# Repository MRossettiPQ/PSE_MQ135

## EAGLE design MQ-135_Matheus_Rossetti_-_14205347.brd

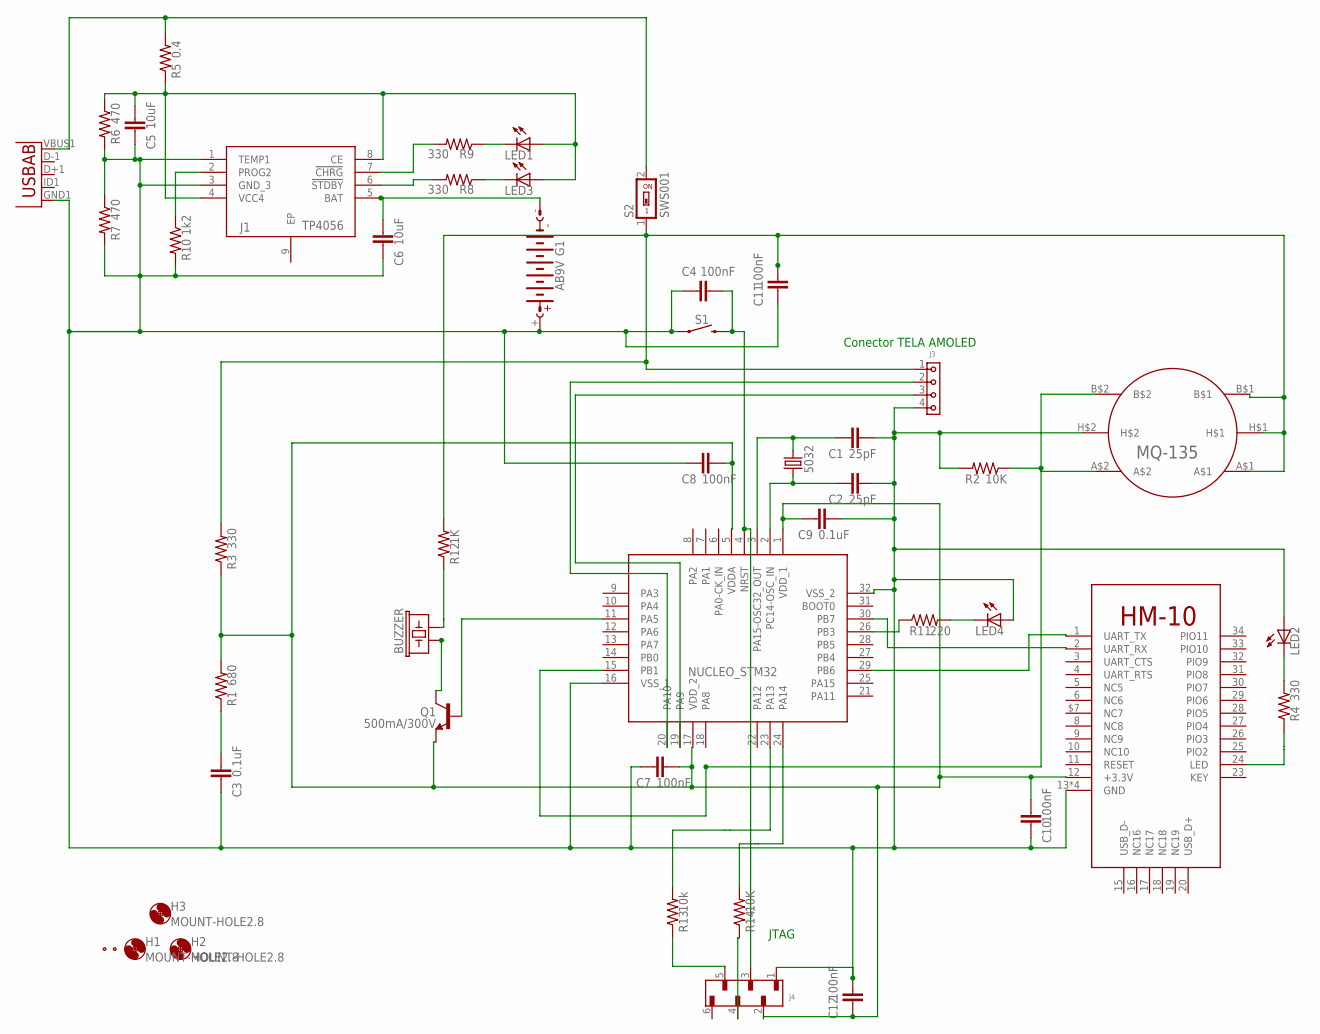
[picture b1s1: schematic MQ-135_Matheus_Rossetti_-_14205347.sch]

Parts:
BT_SENSOR: HM-10-BOARD; 26.9X13X2.2_BOARD
C1, C2: 25pF; CAP_0805
C3, C9: 0.1uF; CAP_0805
C4, C7, C8, C10, C11, C12: 100nF; CAP_0805
C5, C6: 10uF; CAP_0805
G1: AB9V
H1, H2, H3: MOUNT-HOLE2.8; 2,8
J1: TP4056; SOIC127P600X175-9N
J3: 6130XX11821_61300411821; 61300411821
J4: 6100XX18221_61000618221; 61000618221
LED1, LED2, LED3, LED4: LEDCHIP-LED0805; CHIP-LED0805
LS4: BUZZER; BUZZER-CCV-KIT
NUCLEO_STM32: STM32; QFP80P900X900X160-32N
Q1: 500mA/300V; SOT23-3
R1: 680; RES_0805
R2, R14: 10K; RES_0805
R3, R4, R8, R9: 330; RES_0805
R5: 0.4; RES_0805
R6, R7: 470; RES_0805
R10: 1k2; RES_0805
R11: 220; RES_0805
R12: 1K; RES_0805
R13: 10k; RES_0805
S1: MOMENTARY-SWITCH-SPST-SMD-6.0X3.5MM; TACTILE_SWITCH_SMD_6.0X3.5MM
S2: SWS001; SMS-001
U1: USB""; USB-MICRO-SMD
U$1: MQ_135_A; MQ-135
X1, X3: FIDUCIAL_0.6-1.2MM; FIDUCIAL0.6-1.2
X2: 5032; 5032/2P

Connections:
3,3V: BT_SENSOR.12 (+3.3V), C7.1, C8.1, C9.2, C10.1, C12.1, J4.2, NUCLEO_STM32.1 (VDD_1), NUCLEO_STM32.5 (VDDA), NUCLEO_STM32.17 (VDD_2), Q1.2 (E), R1.2, R3.1
5V: R5.2, S2.2, U1.VBUS1 (VBUS)
5V-SWT: C11.2, J3.1, R3.2, R12.2, S2.1, U$1.A$1, U$1.B$1, U$1.H$1
ENTRADASENSOR: NUCLEO_STM32.15 (PB1), R2.1, U$1.A$2, U$1.B$2
GND: BT_SENSOR.13 (GND), BT_SENSOR.14 (GND), BT_SENSOR.21 (GND), BT_SENSOR.22 (GND), C1.2, C2.2, C3.2, C4.1, C5.2, C6.1, C7.2, C8.2, C9.1, C10.2, C11.1, C12.2, G1.+, J1.1 (TEMP1), J1.3 (GND_3), J3.4, J4.1, LED2.A, LED4.A, NUCLEO_STM32.16 (VSS_1), NUCLEO_STM32.32 (VSS_2), R2.2, R6.2, R7.1, R7.2, R10.2, S1.1, U1.GND1 (GND), U$1.H$2
unnamed: NUCLEO_STM32.23 (PA13), R13.2
unnamed: NUCLEO_STM32.11 (PA5), Q1.1 (B)
unnamed: NUCLEO_STM32.24 (PA14), R14.2
unnamed: J4.5, R13.1
unnamed: NUCLEO_STM32.26 (PB3), R11.1
unnamed: BT_SENSOR.2 (UART_RX), NUCLEO_STM32.30 (PB7)
unnamed: BT_SENSOR.24 (LED), R4.1
unnamed: C1.1, NUCLEO_STM32.3 (PA15-OSC32_OUT), X2.2
unnamed: C6.2, G1.-, J1.5 (BAT)
unnamed: C2.1, NUCLEO_STM32.2 (PC14-OSC_IN), X2.1
unnamed: LED2.C, R4.2
unnamed: J3.2, NUCLEO_STM32.20 (PA10)
unnamed: C5.1, J1.4 (VCC4), J1.8 (CE), LED1.A, LED3.A, R5.1, R6.1
unnamed: J4.4, R14.1
unnamed: J3.3, NUCLEO_STM32.19 (PA9)
unnamed: J1.2 (PROG2), R10.1
unnamed: LED4.C, R11.2
unnamed: LS4.+ (1), Q1.3 (C)
unnamed: C3.1, R1.1
unnamed: LS4.- (2), R12.1
unnamed: BT_SENSOR.1 (UART_TX), NUCLEO_STM32.29 (PB6)
unnamed: J1.6 (!STDBY), R8.2
unnamed: J1.7 (!CHRG), R9.2
unnamed: LED1.C, R9.1
unnamed: LED3.C, R8.1
RST: C4.2, J4.3, NUCLEO_STM32.4 (NRST), S1.2

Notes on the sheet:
Conector TELA AMOLED
JTAG

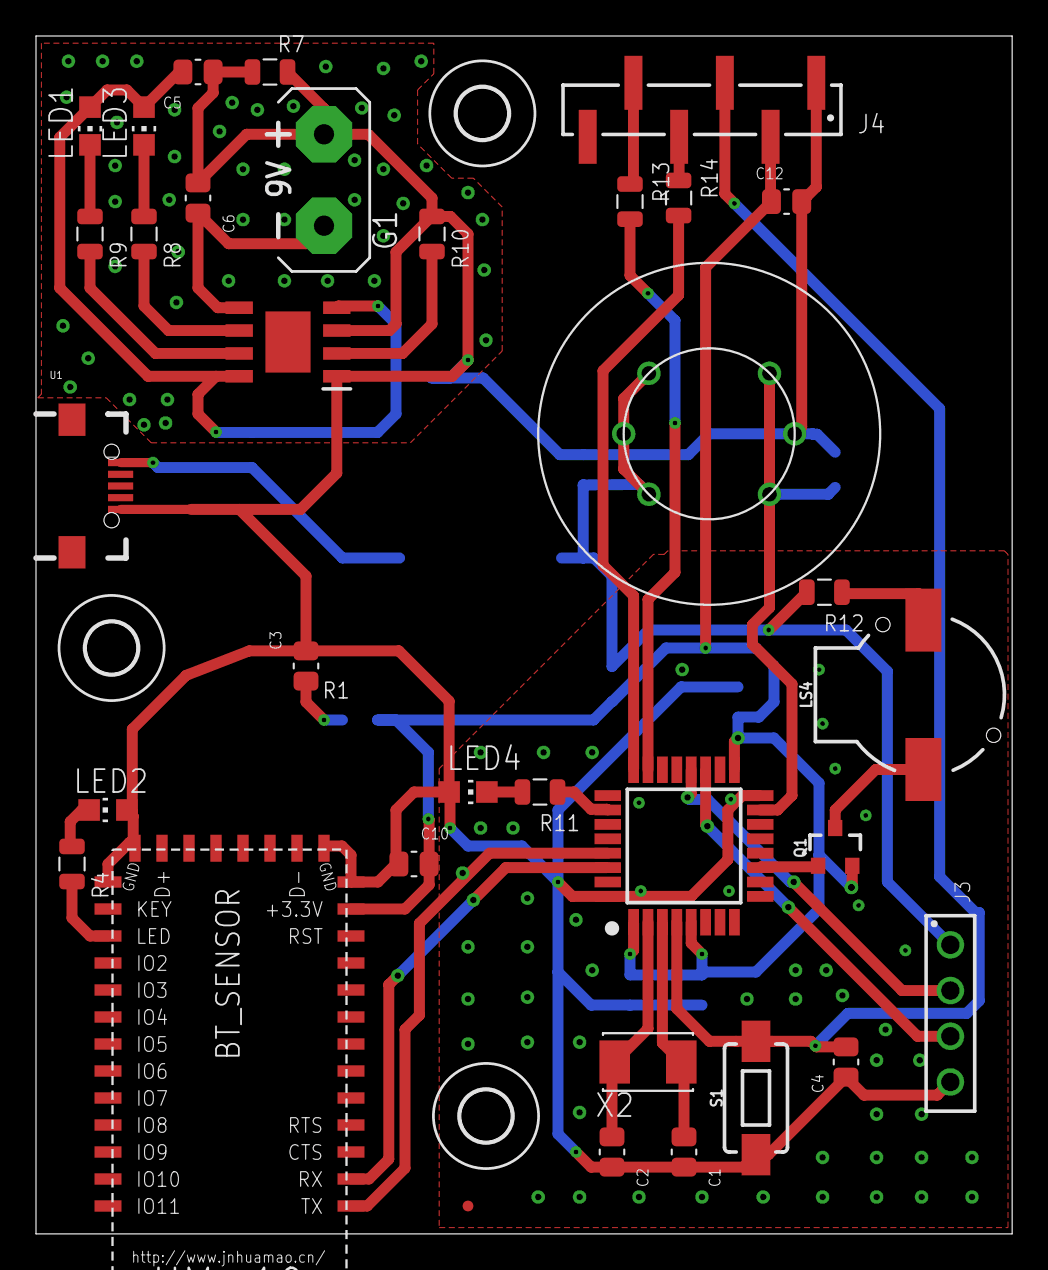
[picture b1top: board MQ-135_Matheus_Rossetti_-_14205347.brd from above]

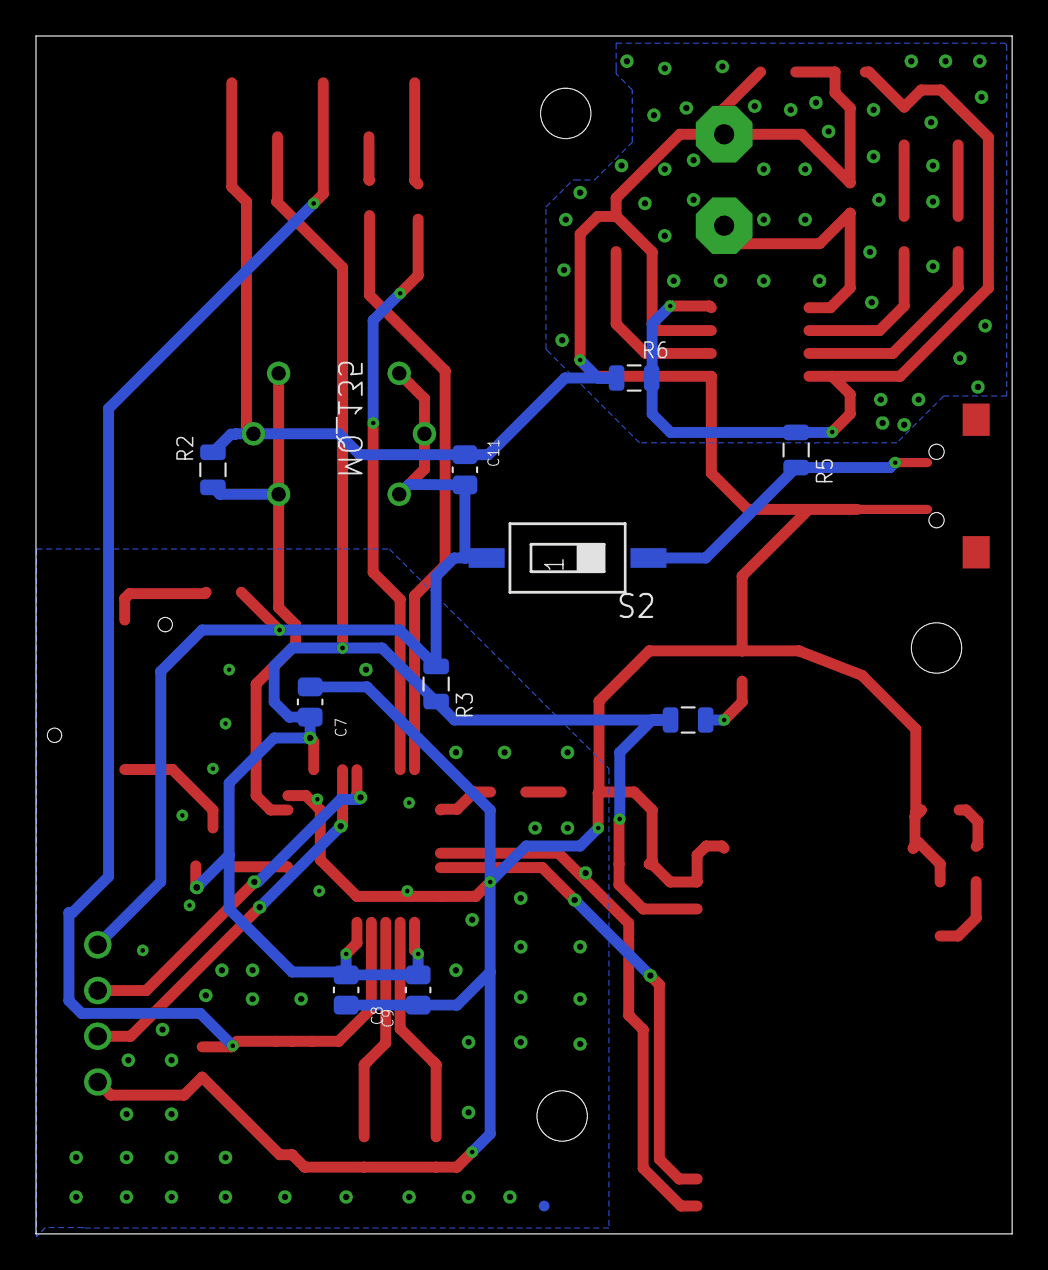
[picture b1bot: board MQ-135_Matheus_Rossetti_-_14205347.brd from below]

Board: 2 copper layers, 54.2 x 66.5 mm, 48 parts (11 on the bottom side), 31 nets.

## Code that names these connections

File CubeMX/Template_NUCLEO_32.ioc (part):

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Mcu.Name=STM32L031K(4-6)Tx
Mcu.Package=LQFP32
Mcu.UserName=STM32L031K6Tx
PA10.GPIOParameters=GPIO_Label
PA10.GPIO_Label=I2C_SDA
PA10.Mode=I2C
PA10.Signal=I2C1_SDA
PA13.GPIOParameters=GPIO_Label
PA13.GPIO_Label=TMS
PA13.Mode=Serial_Wire
PA13.Signal=SYS_SWDIO
PA14.GPIOParameters=GPIO_Label
PA14.GPIO_Label=TCK
PA14.Mode=Serial_Wire
PA14.Signal=SYS_SWCLK
PA5.GPIOParameters=GPIO_Label
PA5.GPIO_Label=BUZZ_OUT
PA5.Signal=GPIO_Output
PA9.GPIOParameters=GPIO_Label
PA9.GPIO_Label=I2C_SCL
PA9.Mode=I2C
PA9.Signal=I2C1_SCL
PB1.GPIOParameters=GPIO_Label
PB1.GPIO_Label=ADC_SEN
PB1.Mode=IN9
PB1.Signal=ADC_IN9
PB3.GPIOParameters=GPIO_Label
PB3.GPIO_Label=LD3 [Green]
PB3.Signal=GPIO_Output
PB6.GPIOParameters=GPIO_Label
PB6.GPIO_Label=BLE_TX
PB6.Mode=Asynchronous
PB6.Signal=USART2_TX
PB7.GPIOParameters=GPIO_Label
PB7.GPIO_Label=BLE_RX
PB7.Mode=Asynchronous
PB7.Signal=USART2_RX
PC14-OSC32_IN.Mode=LSE-External-Oscillator
PC14-OSC32_IN.Signal=RCC_OSC32_IN
PC15-OSC32_OUT.Mode=LSE-External-Oscillator
PC15-OSC32_OUT.Signal=RCC_OSC32_OUT
RCC.HSE_VALUE=8000000
RCC.SYSCLKFreq_VALUE=32000000
RCC.SYSCLKSource=RCC_SYSCLKSOURCE_PLLCLK
board=NUCLEO-L031K6
boardIOC=true

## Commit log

2021-05-06 1.0.060520211416
2021-05-09 1.08052021.2336
2021-05-10 2.09052021.2212
2021-05-10 2.09052021.2215
2021-05-10 2.09052021.2235

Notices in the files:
parts and their libraries:
SparkFun-Switches: Licensing: Creative Commons ShareAlike 4.0 International - https://creativecommons.org/licenses/by-sa/4.0
Wurth_Connectors_WR-PHD: Copyright: Würth Elektronik
